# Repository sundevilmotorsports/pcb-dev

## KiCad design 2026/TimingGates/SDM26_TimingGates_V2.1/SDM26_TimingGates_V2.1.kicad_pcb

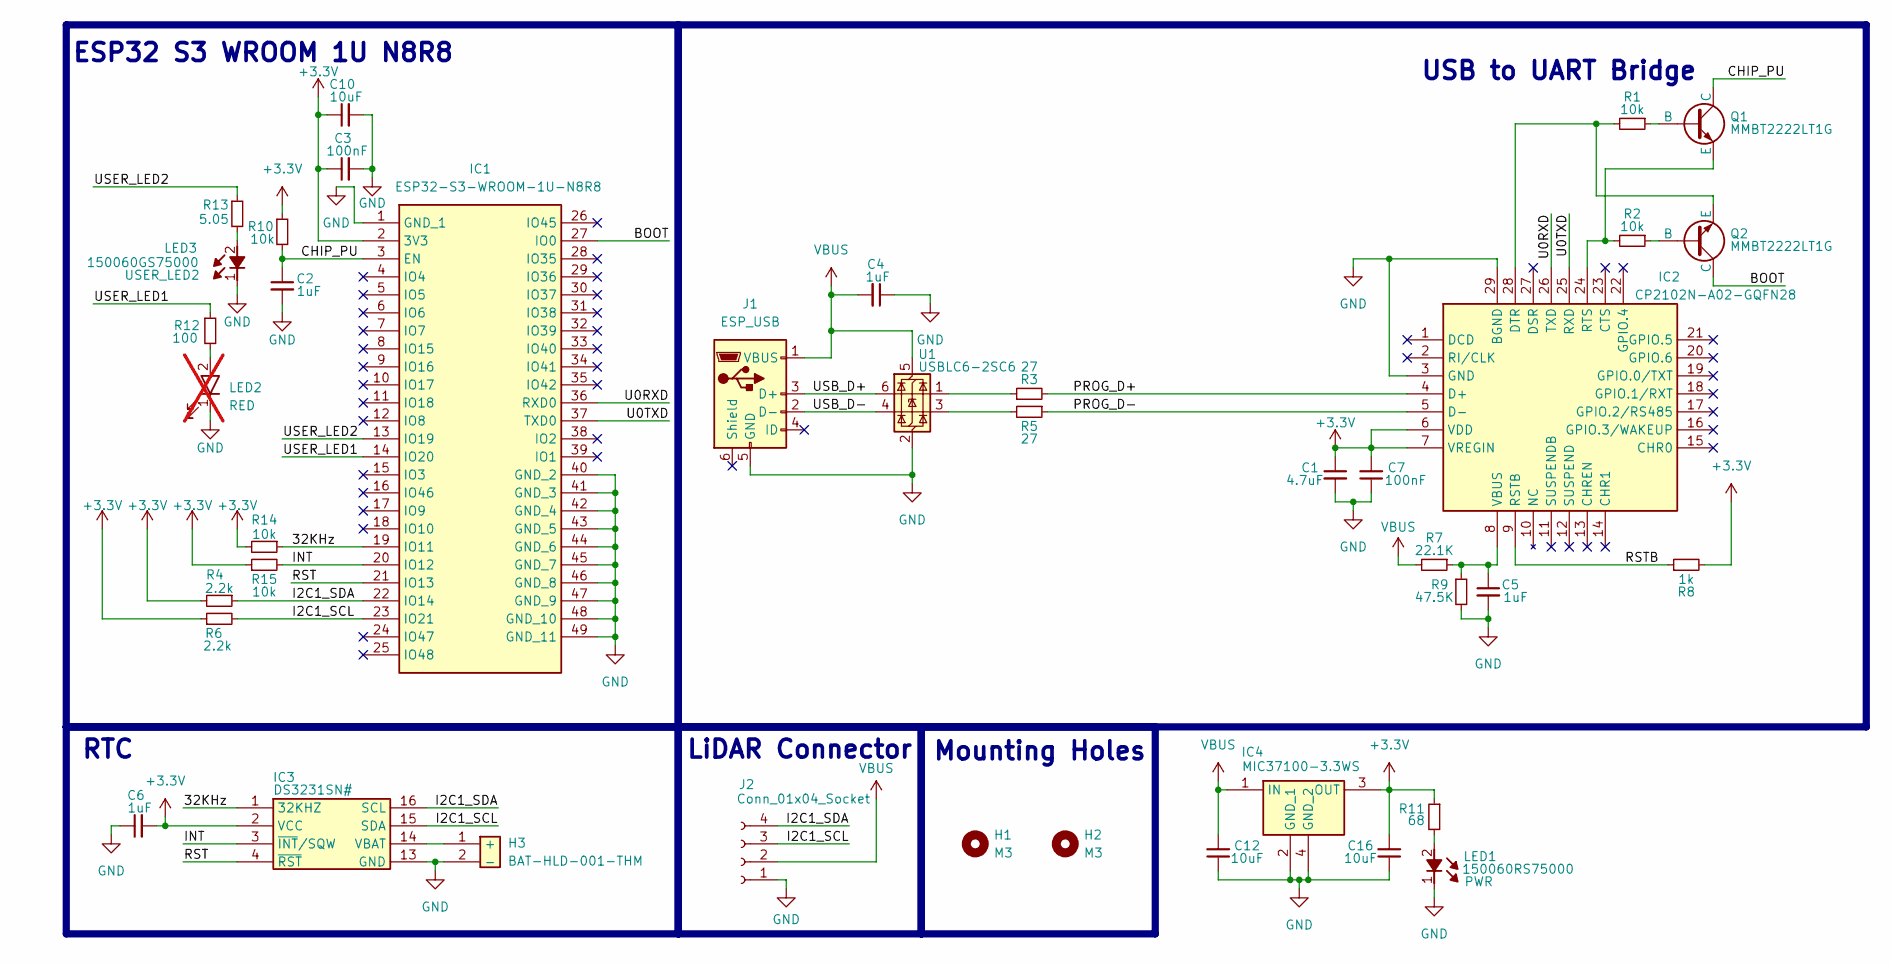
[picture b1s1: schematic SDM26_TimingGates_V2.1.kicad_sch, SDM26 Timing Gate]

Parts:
C1: 4.7uF; C_0603_1608Metric
C2, C4, C5, C6: 1uF; C_0603_1608Metric
C3, C7: 100nF; C_0603_1608Metric
C10, C12, C16: 10uF; C_0603_1608Metric
H1, H2: M3; MountingHole_3.2mm_M3
H3: BAT-HLD-001-THM; BATHLD001THM; Mouser Part Number N/A
IC1: ESP32-S3-WROOM-1U-N8R8; ESP32S3WROOM1UN8R8; Mouser Part Number 356-ESP32S3WRM1UN8R8
IC2: CP2102N-A02-GQFN28; QFN50P500X500X80-29N-D; Mouser Part Number 634-CP2102NA02GQFN28
IC3: DS3231SN#; SOIC127P1032X265-16L; Mouser Part Number 700-DS3231SN#
IC4: MIC37100-3.3WS; SOT230P700X180-4N; Mouser Part Number 998-MIC37100-3.3WS
J1: ESP_USB; USB_Micro-B_Molex-105017-0001
J2: Conn_01x04_Socket; JST_XH_B4B-XH-A_1x04_P2.50mm_Vertical
LED1: 150060RS75000; LEDC1608X80N; Mouser Part Number 710-150060RS75000
LED2: RED; SSFLXH100LID01; Mouser Part Number 696-SSFLXH100LID01; not fitted
LED3: 150060GS75000; LEDC1608X80N; Mouser Part Number 710-150060GS75000
Q1, Q2: MMBT2222LT1G; SOT96P237X111-3N
R1, R2, R10, R14, R15: 10k; R_0603_1608Metric
R3, R5: 27; R_0603_1608Metric
R4, R6: 2.2k; R_0603_1608Metric
R7: 22.1K; R_0603_1608Metric
R8: 1k; R_0603_1608Metric
R9: 47.5K; R_0603_1608Metric
R11: 68; R_0603_1608Metric
R12: 100; R_0603_1608Metric
R13: 5.05; R_0603_1608Metric
U1: USBLC6-2SC6; SOT-23-6

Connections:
+3.3V: C1.1, C3.1, C6.2, C7.2, C10.1, C16.2, IC1.2 (3V3), IC2.6 (VDD), IC2.7 (VREGIN), IC3.2 (VCC), IC4.3 (OUT), R4.2, R6.1, R8.2, R10.1, R11.1, R14.2, R15.1
/32KHz: IC1.19 (IO11), IC3.1 (32KHZ), R14.1
/BOOT: IC1.27 (IO0), Q2.3 (C)
/CHIP_PU: C2.1, IC1.3 (EN), Q1.3 (C), R10.2
/I2C1_SCL: IC1.23 (IO21), IC3.15 (SDA), J2.3, R6.2
/I2C1_SDA: IC1.22 (IO14), IC3.16 (SCL), J2.4, R4.1
/INT: IC1.20 (IO12), IC3.3 (~INT/SQW), R15.2
/PROG_D+: IC2.4 (D+), R3.2
/PROG_D-: IC2.5 (D-), R5.1
/RST: IC1.21 (IO13), IC3.4 (~RST)
/RSTB: IC2.9 (RSTB), R8.1
/U0RXD: IC1.36 (RXD0), IC2.26 (TXD)
/U0TXD: IC1.37 (TXD0), IC2.25 (RXD)
/USB_D+: J1.3 (D+), U1.6 (I/O1)
/USB_D-: J1.2 (D-), U1.4 (I/O2)
/USER_LED1: IC1.14 (IO20), R12.1
/USER_LED2: IC1.13 (IO19), R13.1
GND: C1.2, C2.2, C3.2, C4.1, C5.2, C6.1, C7.1, C10.2, C12.1, C16.1, H3.2 (-), IC1.1 (GND_1), IC1.40 (GND_2), IC1.41 (GND_3), IC1.42 (GND_4), IC1.43 (GND_5), IC1.44 (GND_6), IC1.45 (GND_7), IC1.46 (GND_8), IC1.47 (GND_9), IC1.48 (GND_10), IC1.49 (GND_11), IC2.3 (GND), IC2.29 (BGND), IC3.13 (GND), IC4.2 (GND_1), IC4.4 (GND_2), J1.5 (GND), J2.1, LED1.1 (K), LED2.1 (K), LED3.1 (K), R9.2, U1.2 (GND)
unnamed: H3.1 (+), IC3.14 (VBAT)
unnamed: IC2.28 (DTR), Q2.2 (E), R1.2
unnamed: IC2.24 (RTS), Q1.2 (E), R2.2
unnamed: C5.1, IC2.8 (VBUS), R7.1, R9.1
unnamed: LED1.2 (A), R11.2
unnamed: LED2.2 (A), R12.2
unnamed: LED3.2 (A), R13.2
unnamed: Q1.1 (B), R1.1
unnamed: Q2.1 (B), R2.1
unnamed: R3.1, U1.1 (I/O1)
unnamed: R5.2, U1.3 (I/O2)
VBUS: C4.2, C12.2, IC4.1 (IN), J1.1 (VBUS), J2.2, R7.2, U1.5 (VBUS)

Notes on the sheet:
ESP32 S3 WROOM 1U N8R8
RTC
USB to UART Bridge
Mounting Holes
LiDAR Connector

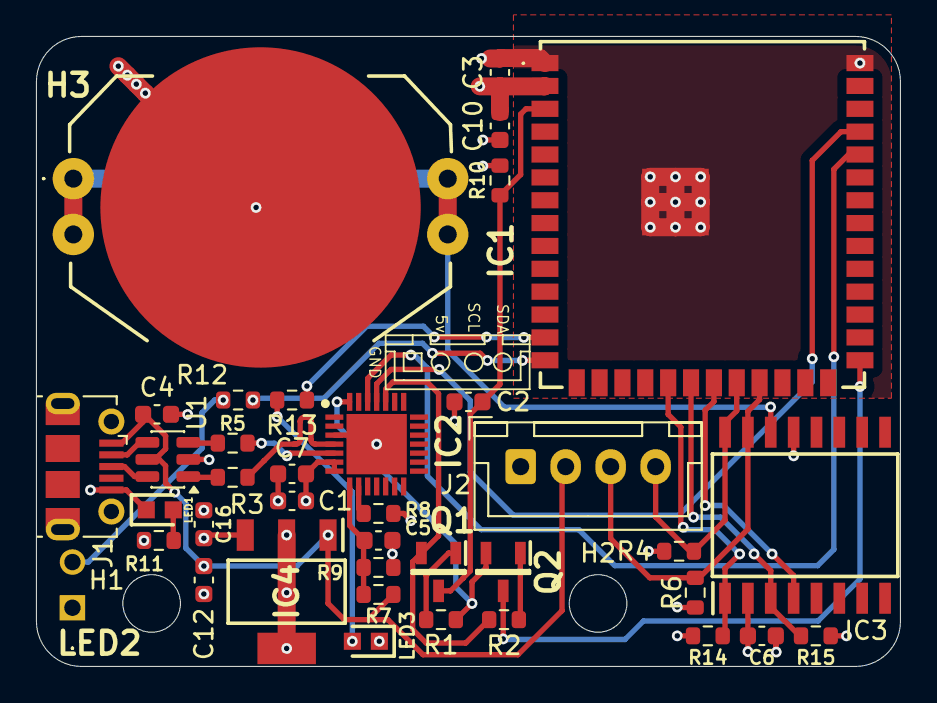
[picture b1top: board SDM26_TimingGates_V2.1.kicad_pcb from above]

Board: 4 copper layers, 48.0 x 35.0 mm, 40 parts (1 on the bottom side), 30 nets.

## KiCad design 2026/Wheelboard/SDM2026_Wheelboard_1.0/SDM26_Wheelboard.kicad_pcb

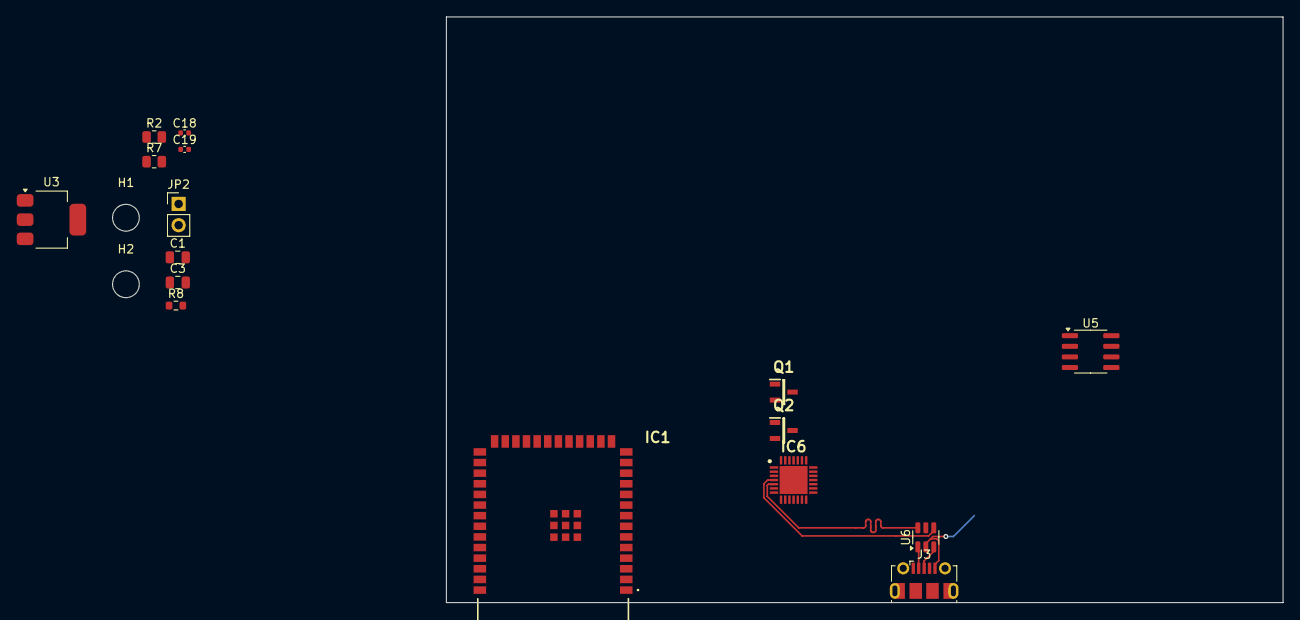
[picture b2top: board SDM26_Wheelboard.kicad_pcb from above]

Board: 4 copper layers, 100.0 x 70.0 mm, 18 parts (0 on the bottom side), 11 nets.

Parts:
C1, C3: 10uF; C_0805_2012Metric
C18, C19: 100nF; C_0402_1005Metric
H1, H2: M3; MountingHole_3.2mm_M3
IC1: ESP32-S3-WROOM-1-N8R8; ESP32S3WROOM1N8R8
IC6: CP2102N-A02-GQFN28; QFN50P500X500X80-29N-D
J3: USB_B_Micro; USB_Micro-B_Molex-105017-0001
JP2: Bus Termination; PinHeader_1x02_P2.54mm_Vertical
Q1, Q2: SOT96P237X111-3N
R2: 220; R_0805_2012Metric
R7: 10k; R_0805_2012Metric
R8: 120; R_0603_1608Metric
U3: MIC37100-3.3WS; SOT-223-3_TabPin2
U5: SN65HVD230; SOIC-8_3.9x4.9mm_P1.27mm
U6: USBLC6-2SC6; SOT-23-6

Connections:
+3.3V: C3.1, C18.1, C19.1, IC6.6 (VDD), IC6.7 (VREGIN), U3.3 (OUT), U5.3 (VCC)
/CAN+: R8.1, U5.7 (CANH)
/CAN-: JP2.1 (A), U5.6 (CANL)
/CAN_Rs: R7.1, U5.8 (Rs)
/USB_D+: IC6.4 (D+), U6.4 (I/O2)
/USB_D-: IC6.5 (D-), U6.6 (I/O1)
/USB_J_D+: J3.3 (D+), U6.3 (I/O2)
/USB_J_D-: J3.2 (D-), U6.1 (I/O1)
GND: C1.2, C3.2, C18.2, C19.2, IC6.3 (GND), IC6.29 (BGND), J3.5 (GND), R2.2, R7.2, U3.2 (GND), U5.2 (GND), U6.2 (GND)
unnamed: JP2.2 (B), R8.2
VCC: C1.1, J3.1 (VBUS), U3.1 (IN), U6.5 (VBUS)

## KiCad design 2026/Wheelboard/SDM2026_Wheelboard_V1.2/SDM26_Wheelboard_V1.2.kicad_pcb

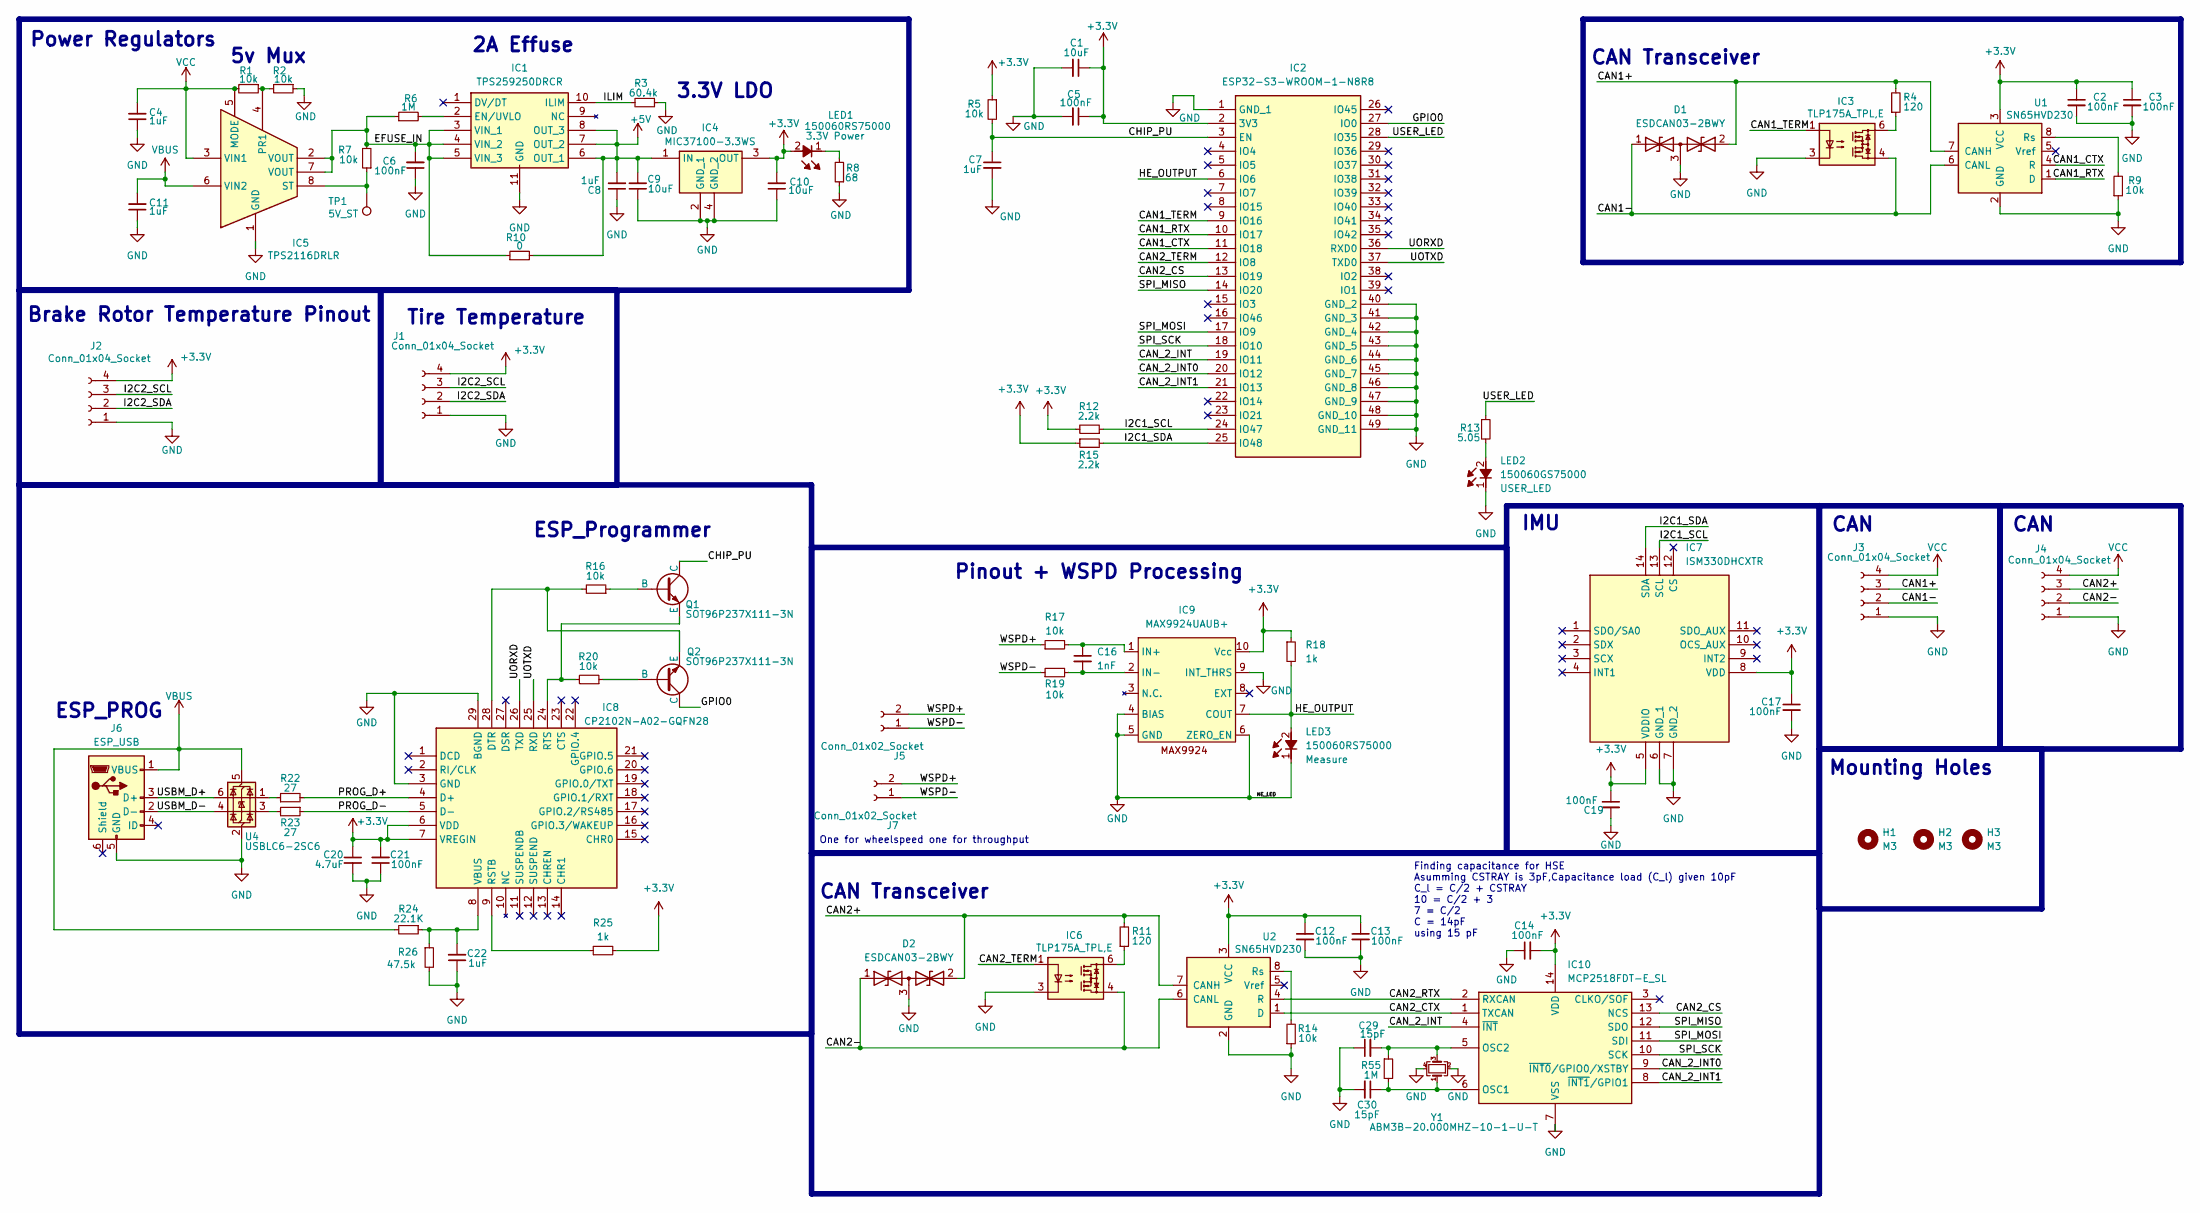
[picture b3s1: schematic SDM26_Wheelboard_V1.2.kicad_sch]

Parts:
C1, C9, C10: 10uF; C_0603_1608Metric
C2, C3, C5, C6, C12, C13, C14, C17, C19, C21: 100nF; C_0603_1608Metric
C4, C7, C8, C11, C22: 1uF; C_0603_1608Metric
C16: 1nF; C_0603_1608Metric
C20: 4.7uF; C_0603_1608Metric
C29, C30: 15pF; C_0603_1608Metric
D1, D2: ESDCAN03-2BWY; SOT65P210X110-3N; Mouser Part Number 511-ESDCAN03-2BWY
H1, H2, H3: M3; MountingHole_3.2mm_M3
IC1: TPS259250DRCR; SON50P300X300X100-11L-D; Mouser Part Number 595-TPS259250DRCR
IC2: ESP32-S3-WROOM-1-N8R8; ESP32S3WROOM1N8R8; Mouser Part Number 356-EP32S3WROOM1N8R8
IC3, IC6: TLP175A_TPL,E; TLP266J; Mouser Part Number 757-TLP175A(TPLE
IC4: MIC37100-3.3WS; SOT230P700X180-4N; Mouser Part Number 998-MIC37100-3.3WS
IC5: TPS2116DRLR; SOTFL50P160X60-8L; Mouser Part Number 595-TPS2116DRLR
IC7: ISM330DHCXTR; LSM6DS3USTR; Mouser Part Number 511-ISM330DHCXTR
IC8: CP2102N-A02-GQFN28; QFN50P500X500X80-29N-D; Mouser Part Number 634-CP2102NA02GQFN28
IC9: MAX9924UAUB+; SOP50P490X110-10L; Mouser Part Number 700-MAX9924UAUB
IC10: MCP2518FDT-E_SL; SOIC127P600X175-14L; Mouser Part Number 579-MCP2518FDT-E/SL
J1, J2, J3, J4: Conn_01x04_Socket; JST_XH_S4B-XH-A_1x04_P2.50mm_Horizontal
J5, J7: Conn_01x02_Socket; JST_XH_S2B-XH-A_1x02_P2.50mm_Horizontal
J6: ESP_USB; USB_Micro-B_Molex-105017-0001
LED1, LED3: 150060RS75000; LEDC1608X80N; Mouser Part Number 710-150060RS75000
LED2: 150060GS75000; LEDC1608X80N; Mouser Part Number 710-150060VS75000
Q1, Q2: SOT96P237X111-3N
R1, R2, R5, R7, R9, R14, R16, R20: 10k; R_0603_1608Metric
R3: 60.4k; R_0603_1608Metric
R4, R11: 120; R_0603_1608Metric
R6, R55: 1M; R_0603_1608Metric
R8: 68; R_0603_1608Metric
R10: 0; R_0603_1608Metric
R12, R15: 2.2k; R_0603_1608Metric
R13: 5.05; R_0603_1608Metric
R17, R19: 10k; R_0805_2012Metric
R18, R25: 1k; R_0603_1608Metric
R22, R23: 27; R_0603_1608Metric
R24: 22.1K; R_0603_1608Metric
R26: 47.5k; R_0603_1608Metric
TP1: 5V_ST; TestPoint_Pad_1.5x1.5mm
U1, U2: SN65HVD230; SOIC-8_3.9x4.9mm_P1.27mm
U4: USBLC6-2SC6; SOT-23-6
Y1: ABM3B-20.000MHZ-10-1-U-T; ABM3B; Mouser Part Number 815-ABM3B-20-T

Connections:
+3.3V: C1.1, C2.1, C3.1, C5.1, C10.2, C12.1, C13.1, C14.2, C17.1, C19.1, C20.1, C21.2, IC2.2 (3V3), IC4.3 (OUT), IC7.5 (VDDIO), IC7.8 (VDD), IC8.6 (VDD), IC8.7 (VREGIN), IC9.10 (Vcc), IC10.14 (VDD), J1.4, J2.4, LED1.2 (A), R5.1, R12.2, R15.1, R18.1, R25.2, U1.3 (VCC), U2.3 (VCC)
+5V: C8.2, C9.2, IC1.6 (OUT_1), IC1.7 (OUT_2), IC1.8 (OUT_3), IC4.1 (IN), R10.2
/CAN1+: D1.2, J3.3, R4.2, U1.7 (CANH)
/CAN1-: D1.1, IC3.4, J3.2, U1.6 (CANL)
/CAN1_CTX: IC2.11 (IO18), U1.4 (R)
/CAN1_RTX: IC2.10 (IO17), U1.1 (D)
/CAN1_TERM: IC2.9 (IO16), IC3.1
/CAN2+: D2.2, J4.3, R11.2, U2.7 (CANH)
/CAN2-: D2.1, IC6.4, J4.2, U2.6 (CANL)
/CAN2_CS: IC2.13 (IO19), IC10.13 (NCS)
/CAN2_CTX: IC10.1 (TXCAN), U2.1 (D)
/CAN2_RTX: IC10.2 (RXCAN), U2.4 (R)
/CAN2_TERM: IC2.12 (IO8), IC6.1
/CAN_2_INT: IC2.19 (IO11), IC10.4 (~INT)
/CAN_2_INT0: IC2.20 (IO12), IC10.9 (~INT0/GPIO0/XSTBY)
/CAN_2_INT1: IC2.21 (IO13), IC10.8 (~INT1/GPIO1)
/CHIP_PU: C7.1, IC2.3 (EN), Q1.1 (C), R5.2
/EFUSE_IN: C6.2, IC1.3 (VIN_1), IC1.4 (VIN_2), IC1.5 (VIN_3), IC5.2 (VOUT), IC5.7 (VOUT), R6.1, R7.2, R10.1
/GPIO0: IC2.27 (IO0), Q2.1 (C)
/HE_OUTPUT: IC2.6 (IO6), IC9.7 (COUT), LED3.2 (A), R18.2
/I2C1_SCL: IC2.24 (IO47), IC7.13 (SCL), R12.1
/I2C1_SDA: IC2.25 (IO48), IC7.14 (SDA), R15.2
/I2C2_SCL: J1.3, J2.3
/I2C2_SDA: J1.2, J2.2
/ILIM: IC1.10 (ILIM), R3.2
/PROG_D+: IC8.4 (D+), R22.2
/PROG_D-: IC8.5 (D-), R23.1
/SPI_MISO: IC2.14 (IO20), IC10.12 (SDO)
/SPI_MOSI: IC2.17 (IO9), IC10.11 (SDI)
/SPI_SCK: IC2.18 (IO10), IC10.10 (SCK)
/UORXD: IC2.36 (RXD0), IC8.26 (TXD)
/UOTXD: IC2.37 (TXD0), IC8.25 (RXD)
/USBM_D+: J6.3 (D+), U4.6 (I/O1)
/USBM_D-: J6.2 (D-), U4.4 (I/O2)
/USER_LED: IC2.28 (IO35), R13.1
/WSPD+: J5.2, J7.2, R17.1
/WSPD-: J5.1, J7.1, R19.1
GND: C1.2, C2.2, C3.2, C4.1, C5.2, C6.1, C7.2, C8.1, C9.1, C10.1, C11.1, C12.2, C13.2, C14.1, C17.2, C19.2, C20.2, C21.1, C22.1, C29.1, C30.2, D1.3, D2.3, IC1.11 (GND), IC2.1 (GND_1), IC2.40 (GND_2), IC2.41 (GND_3), IC2.42 (GND_4), IC2.43 (GND_5), IC2.44 (GND_6), IC2.45 (GND_7), IC2.46 (GND_8), IC2.47 (GND_9), IC2.48 (GND_10), IC2.49 (GND_11), IC3.3, IC4.2 (GND_1), IC4.4 (GND_2), IC5.1 (GND), IC6.3, IC7.6 (GND_1), IC7.7 (GND_2), IC8.3 (GND), IC8.29 (BGND), IC9.4 (BIAS), IC9.5 (GND), IC9.6 (ZERO_EN), IC9.9 (INT_THRS), IC10.7 (VSS), J1.1, J2.1, J3.1, J4.1, J6.5 (GND), LED2.1 (K), LED3.1 (K), R2.1, R3.1, R8.1, R9.1, R14.1, R26.2, U1.2 (GND), U2.2 (GND), U4.2 (GND), Y1.2 (GND_1), Y1.4 (GND_2)
unnamed: IC1.2 (EN/UVLO), R6.2
unnamed: IC3.6, R4.1
unnamed: IC5.4 (PR1), R1.1, R2.2
unnamed: IC5.8 (ST), R7.1, TP1.1
unnamed: IC6.6, R11.1
unnamed: IC8.28 (DTR), Q2.3 (E), R16.2
unnamed: IC8.9 (RSTB), R25.1
unnamed: IC8.24 (RTS), Q1.3 (E), R20.2
unnamed: C22.2, IC8.8 (VBUS), R24.1, R26.1
unnamed: C16.1, IC9.1 (IN+), R17.2
unnamed: C16.2, IC9.2 (IN-), R19.2
unnamed: C30.1, IC10.6 (OSC1), R55.2, Y1.1 (XTAL_1)
unnamed: C29.2, IC10.5 (OSC2), R55.1, Y1.3 (XTAL_2)
unnamed: LED1.1 (K), R8.2
unnamed: LED2.2 (A), R13.2
unnamed: Q1.2 (B), R16.1
unnamed: Q2.2 (B), R20.1
unnamed: R22.1, U4.1 (I/O1)
unnamed: R23.2, U4.3 (I/O2)
unnamed: R9.2, U1.8 (Rs)
unnamed: R14.2, U2.8 (Rs)
VBUS: C11.2, IC5.6 (VIN2), J6.1 (VBUS), R24.2, U4.5 (VBUS)
VCC: C4.2, IC5.3 (VIN1), IC5.5 (MODE), J3.4, J4.4, R1.2

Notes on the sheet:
Finding capacitance for HSE Asumming CSTRAY is 3pF,Capacitance load (C_l) given 10pF C_l = C/2 + CSTRAY 10 = C/2 + 3 7 = C/2 C = 14pF using 15 pF
One for wheelspeed one for throughput
2A Effuse
IMU
3.3V LDO
CAN Transceiver
CAN
Brake Rotor Temperature Pinout
ESP_Programmer
ESP_PROG
Pinout + WSPD Processing
5v Mux
Mounting Holes
Tire Temperature
Power Regulators

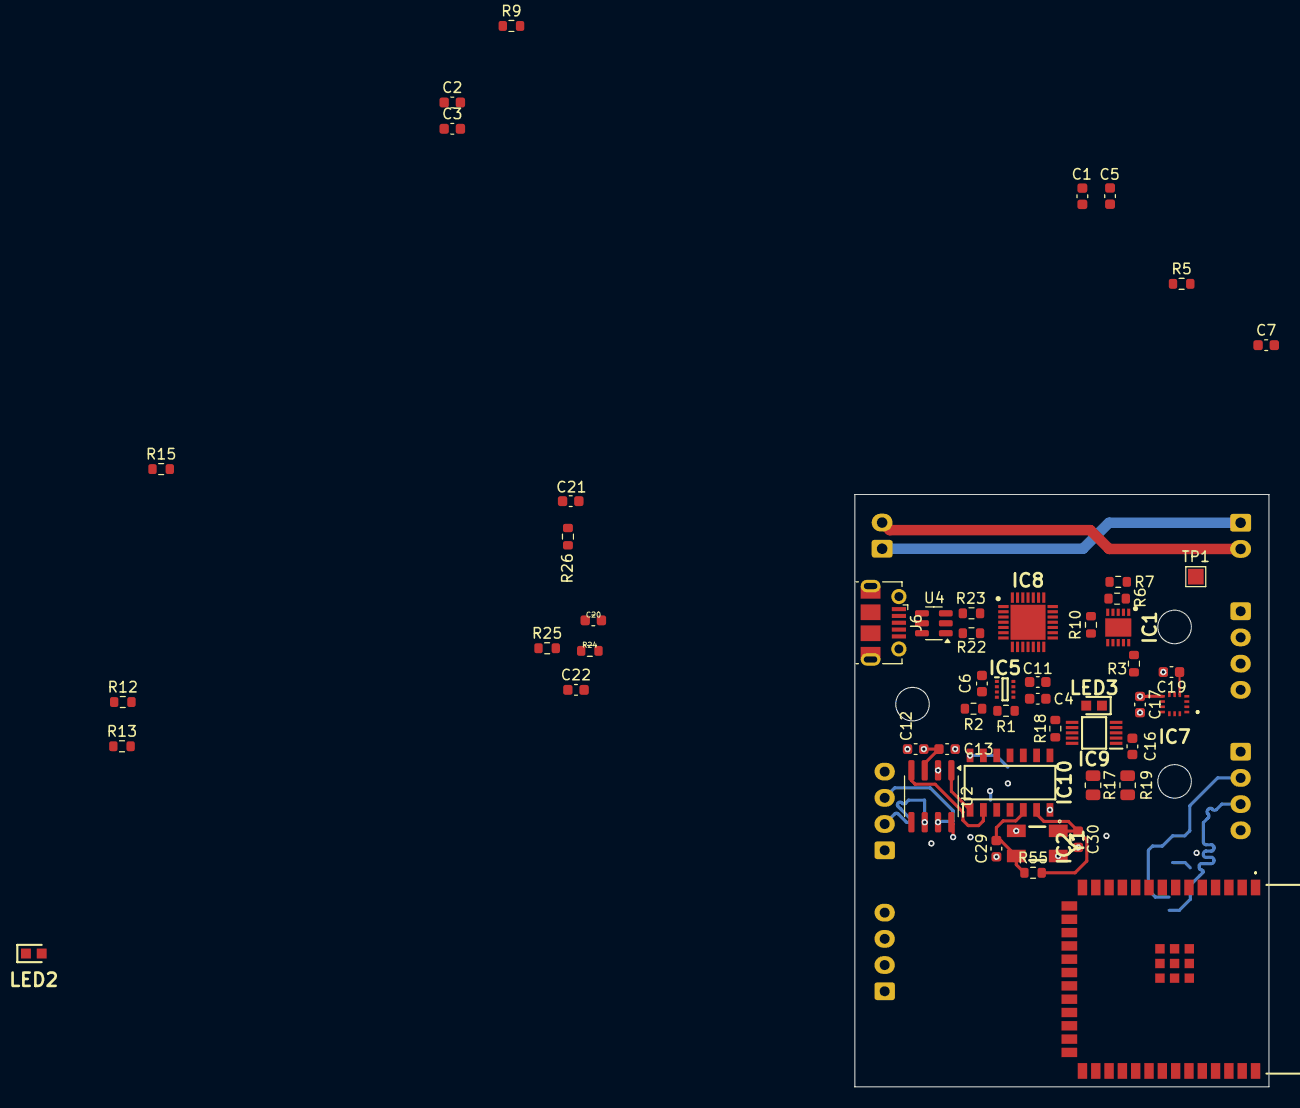
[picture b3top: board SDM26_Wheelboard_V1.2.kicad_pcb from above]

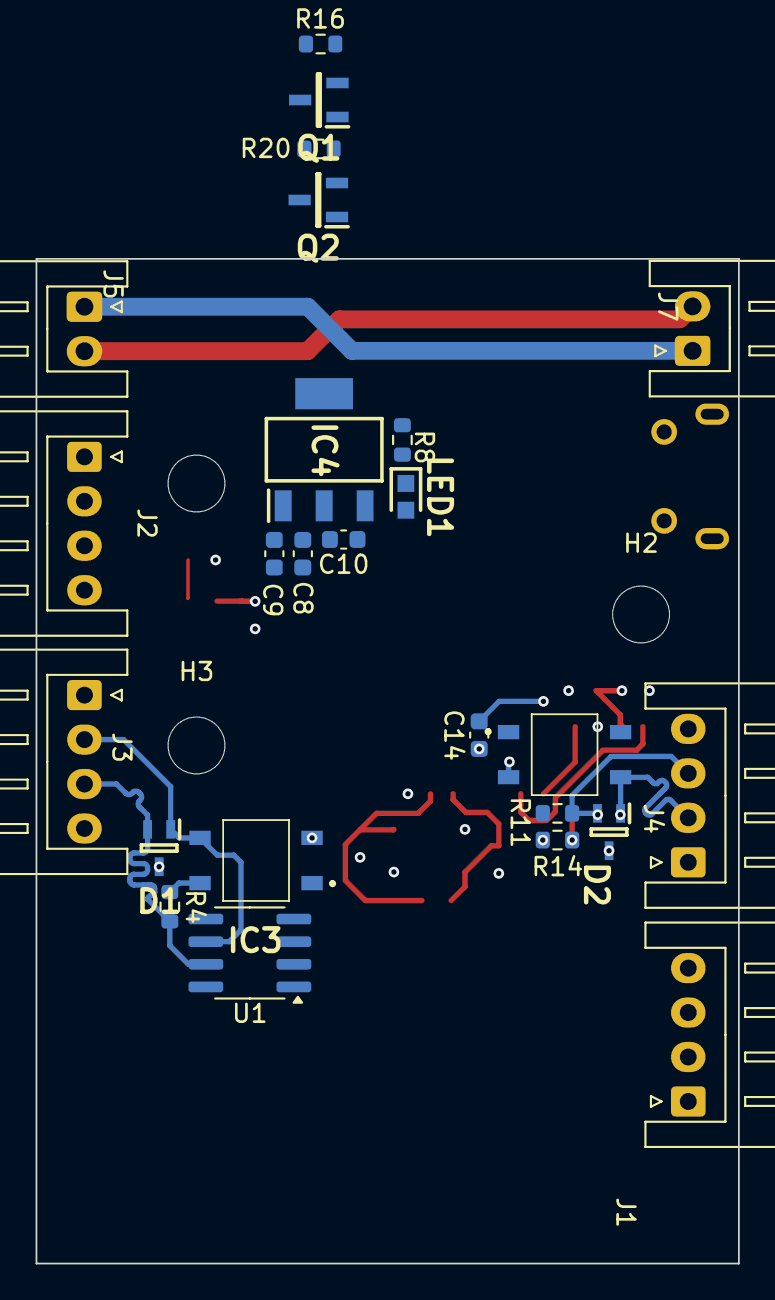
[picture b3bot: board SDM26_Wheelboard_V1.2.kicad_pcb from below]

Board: 4 copper layers, 39.5 x 56.5 mm, 80 parts (28 on the bottom side), 61 nets.
